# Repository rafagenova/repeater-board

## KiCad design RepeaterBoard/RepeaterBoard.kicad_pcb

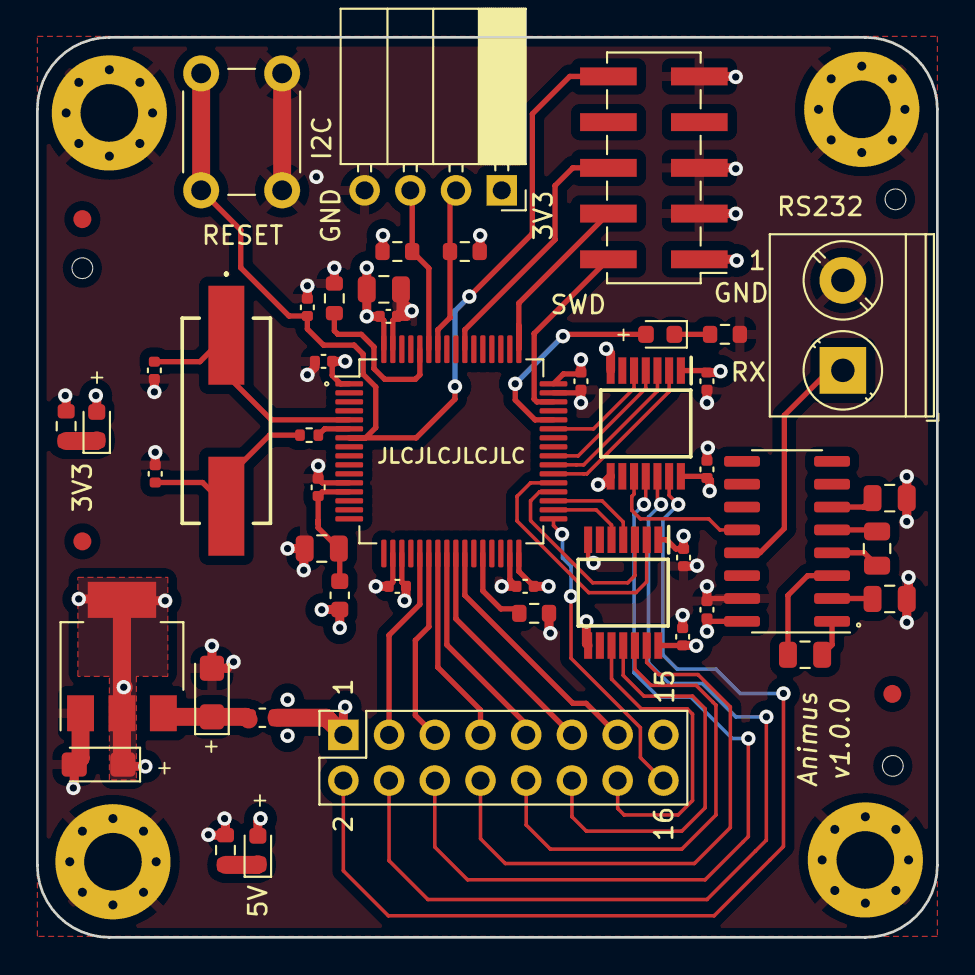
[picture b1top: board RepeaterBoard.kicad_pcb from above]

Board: 4 copper layers, 50.0 x 50.0 mm, 53 parts (0 on the bottom side), 50 nets.

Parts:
C1, C2: 10u/1206; CP_EIA-3216-18_Kemet-A
C3, C9: 10u/0805; C_0805_2012Metric
C4, C5, C6, C7, C8, C11, C18, C19, C20, C21, C22: 100n/0402; C_0402_1005Metric
C10: 10n/0402; C_0402_1005Metric
C12, C13: 20p/0402; C_0402_1005Metric
C14, C15, C16, C17: 1u/0805; C_0805_2012Metric
D1, D2: YELLOW; LED_0603_1608Metric
D3: RED; LED_0603_1608Metric
FB1, FB2: 100@100MHz/0603; L_0603_1608Metric
FID1, FID2, FID3: Fiducial; Fiducial_1mm_Mask2mm
H1, H2, H3, H4: MountingHole_Pad; MountingHole_3.2mm_M3_Pad_Via
HSE1: 8MHz; 830011301
IC1: TXU0104PWR; SOP65P640X120-14N
IC2: TXU0304PWR; SOP65P640X120-14N
J1: Screw_Terminal_01x02; TerminalBlock_Phoenix_PT-1,5-2-5.0-H_1x02_P5.00mm_Horizontal
J2: Conn_01x04; PinSocket_1x04_P2.54mm_Horizontal
J3: Conn_02x08_Odd_Even; PinSocket_2x08_P2.54mm_Vertical
J4: SWD; PinHeader_2x05_P2.54mm_Vertical_SMD
R1, R4, R5: 2k2/0603; R_0603_1608Metric
R2, R8: 1k2/0603; R_0603_1608Metric
R3: 220/0402; R_0402_1005Metric
R6, R7: 10k/0603; R_0603_1608Metric
SW1: SW_Push; SW_PUSH_6mm
U1: AMS1117-3.3; SOT-223-3_TabPin2
U2: MAX232ESE; SOIC127P600X175-16N
U3: STM32F101RBTx; LQFP-64_10x10mm_P0.5mm

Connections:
+3.3VA: C9.1, C10.1, FB2.1, U3.13
+3V3: C2.1, C3.1, C4.1, C5.1, C6.1, C7.1, C8.1, C19.1, C21.1, D2.2, FB2.2, IC1.1, IC1.8, IC2.1, IC2.8, J2.1, J4.1, R4.1, R5.1, U1.2, U3.1, U3.19, U3.32, U3.48, U3.64
+5V: C11.1, C20.1, C22.1, D1.2, FB1.2, IC1.14, IC2.14, J3.1, U2.16
ANODE_A: IC2.4, U3.40
ANODE_A_5V: IC2.11, J3.6
ANODE_B: IC2.3, U3.39
ANODE_B_5V: IC2.12, J3.4
ANODE_C: IC2.2, U3.38
ANODE_C_5V: IC2.13, J3.2
ANODE_D: IC1.2, U3.37
ANODE_DP: J3.16, U3.33
ANODE_D_5V: IC1.13, J3.8
ANODE_E: IC1.3, U3.36
ANODE_E_5V: IC1.12, J3.10
ANODE_F: IC1.4, U3.35
ANODE_F_5V: IC1.11, J3.12
ANODE_G: IC1.5, U3.34
ANODE_G_5V: IC1.10, J3.14
BOOT0: R6.1, U3.60
BOOT1: R7.1, U3.28
DIGIT_1: J3.3, U3.21
DIGIT_2: J3.5, U3.22
DIGIT_3: J3.7, U3.23
DIGIT_4: J3.9, U3.24
DIGIT_5: J3.11, U3.25
DIGIT_6: J3.13, U3.26
GND: C1.2, C2.2, C3.2, C4.2, C5.2, C6.2, C7.2, C8.2, C9.2, C10.2, C11.2, C12.2, C13.2, C16.2, C17.2, C18.2, C19.2, C20.2, C21.2, C22.2, H1.1, H2.1, H3.1, H4.1, IC1.7, IC2.7, J1.2, J2.4, J3.15, J4.3, J4.5, J4.9, R1.2, R2.2, R6.2, R7.2, R8.2, SW1.2, U1.1, U2.15, U3.12, U3.18, U3.31, U3.47, U3.63
I2C1_SCL: J2.2, R4.2, U3.58
I2C1_SDA: J2.3, R5.2, U3.59
NRST: C18.1, J4.10, SW1.1, U3.7
unnamed: C1.1, FB1.1, U1.3
unnamed: C13.1, HSE1.2, R3.2
unnamed: C14.1, U2.1
unnamed: C14.2, U2.3
unnamed: C15.1, U2.4
unnamed: C15.2, U2.5
unnamed: C16.1, U2.2
unnamed: C17.1, U2.6
unnamed: D1.1, R1.1
unnamed: D2.1, R2.1
unnamed: D3.1, R8.1
OSC_IN: C12.1, HSE1.1, U3.5
OSC_OUT: R3.1, U3.6
RX_RS232: J1.1, U2.13
STATUS: D3.2, U3.44
SWCLK: J4.4, U3.49
SWDIO: J4.2, U3.46
SWO: J4.6, U3.55
USART1_RX: IC2.5, U3.43
USART_RX_5V: IC2.10, U2.12

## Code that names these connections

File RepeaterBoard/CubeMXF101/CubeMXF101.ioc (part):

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Mcu.Name=STM32F101R(8-B)Tx
Mcu.Package=LQFP64
Mcu.UserName=STM32F101RBTx
PA10.Mode=Asynchronous
PA10.Signal=USART1_RX
PA11.GPIOParameters=GPIO_Label
PA11.GPIO_Label=STATUS
PA11.Signal=GPIO_Output
PA13.Mode=Trace_Asynchronous_SW
PA13.Signal=SYS_JTMS-SWDIO
PA14.Mode=Trace_Asynchronous_SW
PA14.Signal=SYS_JTCK-SWCLK
PA5.GPIOParameters=GPIO_Label
PA5.GPIO_Label=DIGIT_1
PA5.Signal=GPIO_Output
PA6.GPIOParameters=GPIO_Label
PA6.GPIO_Label=DIGIT_2
PA6.Signal=GPIO_Output
PA7.GPIOParameters=GPIO_Label
PA7.GPIO_Label=DIGIT_3
PA7.Signal=GPIO_Output
PA9.Mode=Asynchronous
PA9.Signal=USART1_TX
PB0.GPIOParameters=GPIO_Label
PB0.GPIO_Label=DIGIT_6
PB0.Signal=GPIO_Output
PB12.GPIOParameters=GPIO_Label
PB12.GPIO_Label=ANODE_DP
PB12.Signal=GPIO_Output
PB13.GPIOParameters=GPIO_Label
PB13.GPIO_Label=ANODE_G
PB13.Signal=GPIO_Output
PB14.GPIOParameters=GPIO_Label
PB14.GPIO_Label=ANODE_F
PB14.Signal=GPIO_Output
PB15.GPIOParameters=GPIO_Label
PB15.GPIO_Label=ANODE_E
PB15.Signal=GPIO_Output
PB2.GPIOParameters=GPIO_Label
PB2.GPIO_Label=BOOT1
PB2.Signal=GPIO_Input
PB3.Mode=Trace_Asynchronous_SW
PB3.Signal=SYS_JTDO-TRACESWO
PB6.Mode=I2C
PB6.Signal=I2C1_SCL
PB7.Mode=I2C
PB7.Signal=I2C1_SDA
PC4.GPIOParameters=GPIO_Label
PC4.GPIO_Label=DIGIT_4
PC4.Signal=GPIO_Output
PC5.GPIOParameters=GPIO_Label
PC5.GPIO_Label=DIGIT_5
PC5.Signal=GPIO_Output
PC6.GPIOParameters=GPIO_Label
PC6.GPIO_Label=ANODE_D
PC6.Signal=GPIO_Output
PC7.GPIOParameters=GPIO_Label
PC7.GPIO_Label=ANODE_C
PC7.Signal=GPIO_Output
PC8.GPIOParameters=GPIO_Label
PC8.GPIO_Label=ANODE_B
PC8.Signal=GPIO_Output
PC9.GPIOParameters=GPIO_Label
PC9.GPIO_Label=ANODE_A
PC9.Signal=GPIO_Output
PD0-OSC_IN.Mode=HSE-External-Oscillator
PD0-OSC_IN.Signal=RCC_OSC_IN
PD1-OSC_OUT.Mode=HSE-External-Oscillator
PD1-OSC_OUT.Signal=RCC_OSC_OUT
board=custom

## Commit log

2022-08-11 add repeater board to git
